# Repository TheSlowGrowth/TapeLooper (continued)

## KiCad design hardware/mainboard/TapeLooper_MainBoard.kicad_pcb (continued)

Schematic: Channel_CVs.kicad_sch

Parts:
C901, C902, C904, C905, C906, C907, C909, C910: 1n; C_0603_1608Metric_Pad1.08x0.95mm_HandSolder
C903, C908: 100n; C_0603_1608Metric_Pad1.08x0.95mm_HandSolder
J901, J902, J903, J904, J905, J906, J907, J908: PJ398SM; THONKICONN
R901, R903, R907, R909, R913, R915, R919, R921: 100k; R_0603_1608Metric_Pad0.98x0.95mm_HandSolder
R902, R908, R914, R920: 78k7; R_0603_1608Metric_Pad0.98x0.95mm_HandSolder
R904, R910, R916, R922: 68k; R_0603_1608Metric_Pad0.98x0.95mm_HandSolder
R905, R911, R917, R923: 481k; R_0603_1608Metric_Pad0.98x0.95mm_HandSolder
R906, R912, R918, R924: 200k; R_0603_1608Metric_Pad0.98x0.95mm_HandSolder
U901, U902: MCP6004; SO-14_3.9x8.65mm_P1.27mm

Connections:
+5VA: J902.2 (TN), J904.2 (TN), J906.2 (TN), J908.2 (TN); also elsewhere on the board
-10V: R905.2, R906.2, R911.2, R912.2, R917.2, R918.2, R923.2, R924.2; also elsewhere on the board
unnamed: J901.3 (T), R901.1
unnamed: J902.3 (T), R903.1
unnamed: J903.3 (T), R907.1
unnamed: J904.3 (T), R909.1
unnamed: J905.3 (T), R913.1
unnamed: J906.3 (T), R915.1
unnamed: J907.3 (T), R919.1
unnamed: J908.3 (T), R921.1
unnamed: C901.1, R901.2, R902.1, R905.1, U901.2 (-)
unnamed: C902.1, R903.2, R904.1, R906.1, U901.6 (-)
unnamed: C904.1, R907.2, R908.1, R911.1, U901.9 (-)
unnamed: C905.1, R909.2, R910.1, R912.1, U901.13 (-)
unnamed: C906.1, R913.2, R914.1, R917.1, U902.2 (-)
unnamed: C907.1, R915.2, R916.1, R918.1, U902.6 (-)
unnamed: C909.1, R919.2, R920.1, R923.1, U902.9 (-)
unnamed: C910.1, R921.2, R922.1, R924.1, U902.13 (-)
PITCH_A: C901.2, R902.2, U901.1; also elsewhere on the board
PITCH_B: C904.2, R908.2, U901.8; also elsewhere on the board
PITCH_C: C906.2, R914.2, U902.1; also elsewhere on the board
PITCH_D: C909.2, R920.2, U902.8; also elsewhere on the board
VOLUME_A: C902.2, R904.2, U901.7; also elsewhere on the board
VOLUME_B: C905.2, R910.2, U901.14; also elsewhere on the board
VOLUME_C: C907.2, R916.2, U902.7; also elsewhere on the board
VOLUME_D: C910.2, R922.2, U902.14; also elsewhere on the board

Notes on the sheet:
Pitch D
Pitch B
Volume D
-2 .. 2V
Volume A
Pitch C
0 .. 5V
Volume B
Pitch A
Volume C

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
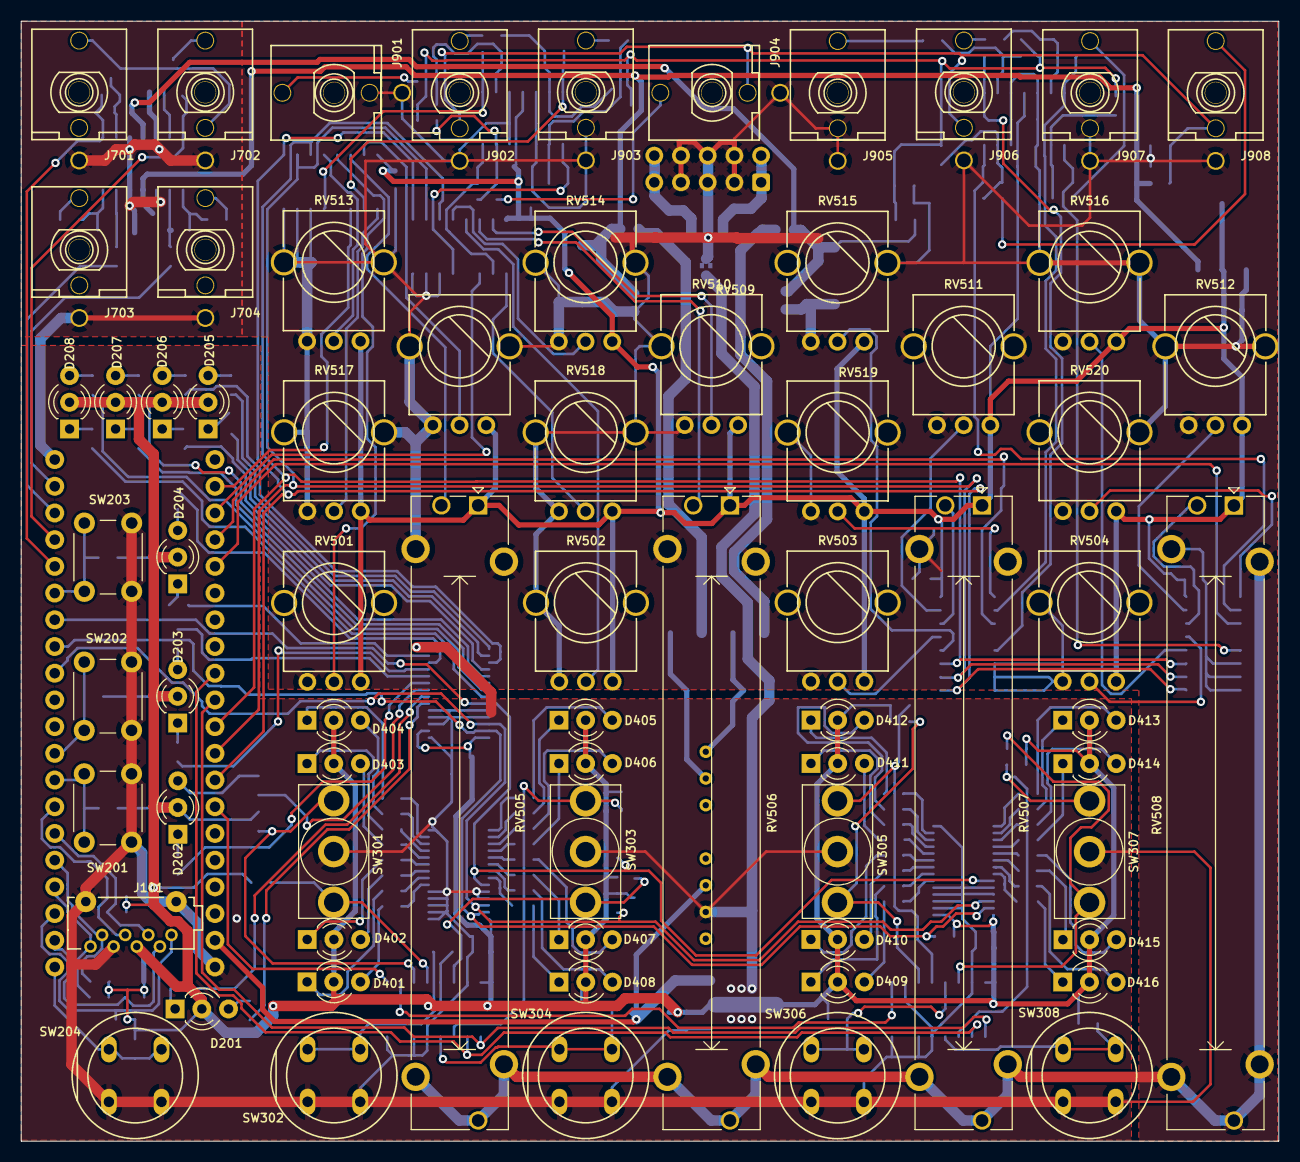
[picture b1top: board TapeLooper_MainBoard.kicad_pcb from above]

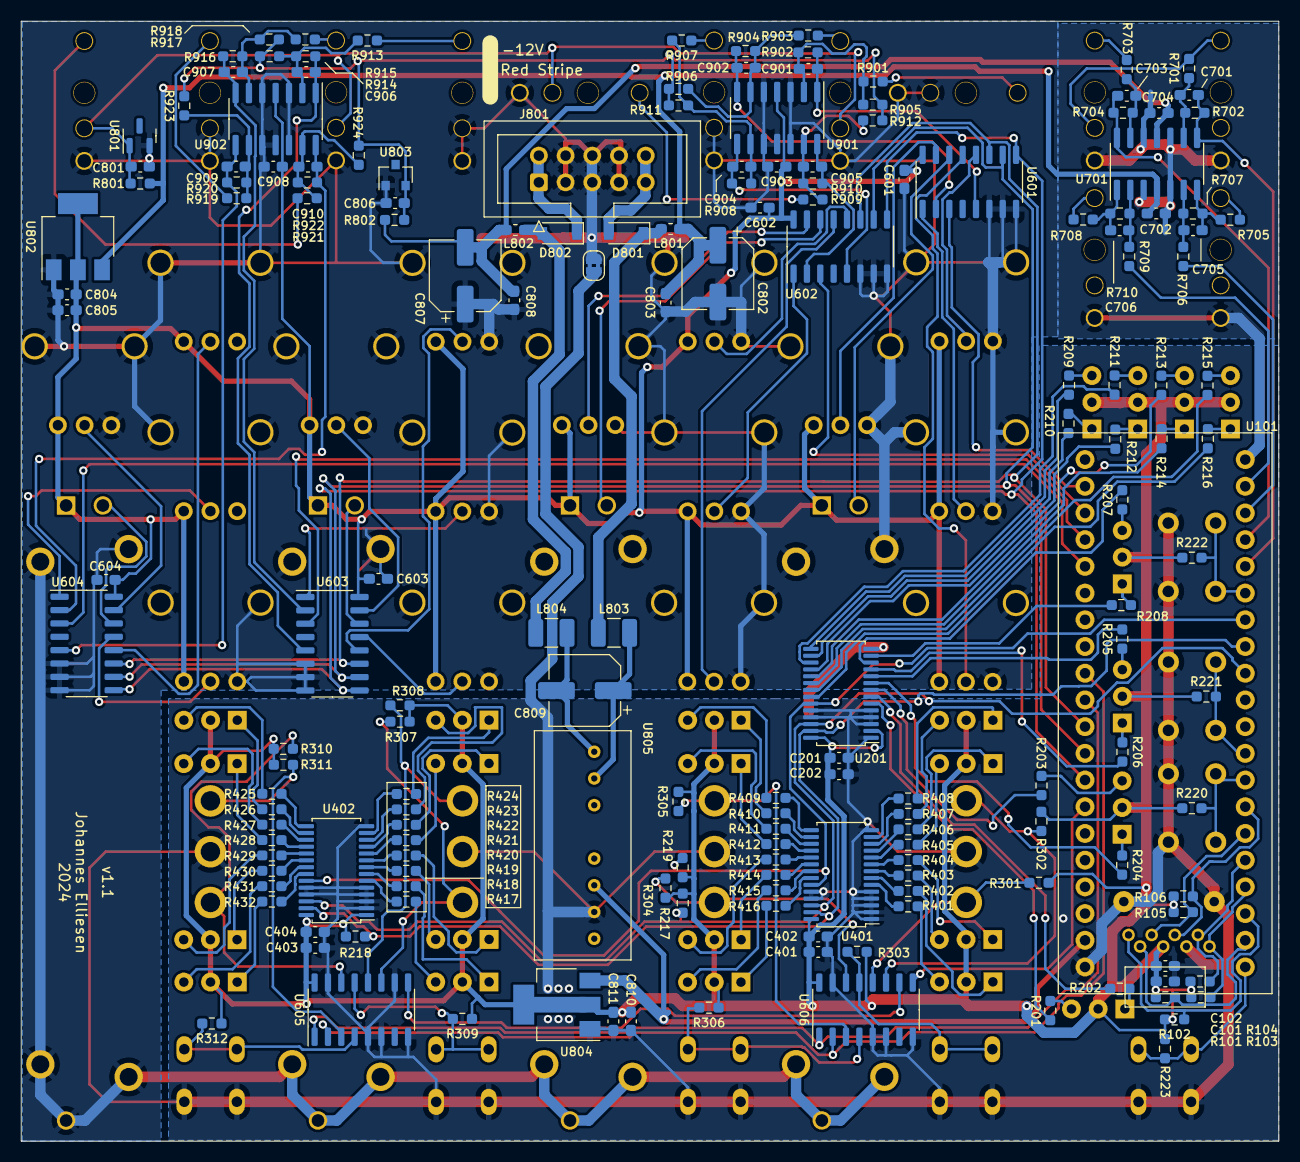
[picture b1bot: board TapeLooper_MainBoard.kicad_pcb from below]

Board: 2 copper layers, 119.6 x 106.5 mm, 243 parts (174 on the bottom side), 205 nets.

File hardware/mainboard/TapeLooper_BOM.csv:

"Reference","Value","Datasheet","Footprint","Qty","DNP"
"C101,C201,C401,C403","10u","","Capacitor_SMD:C_0603_1608Metric_Pad1.08x0.95mm_HandSolder","4",""
"C102,C202,C402,C404,C601,C602,C603,C604,C702,C704,C803,C804,C808,C810,C903,C908","100n","-- mixed values --","Capacitor_SMD:C_0603_1608Metric_Pad1.08x0.95mm_HandSolder","16",""
"C701,C703,C705,C706","560p","","Capacitor_SMD:C_0603_1608Metric_Pad1.08x0.95mm_HandSolder","4",""
"C801,C805,C806,C811","4u7","~","Capacitor_SMD:C_0603_1608Metric_Pad1.08x0.95mm_HandSolder","4",""
"C802,C807,C809","47u","","Capacitor_SMD:CP_Elec_6.3x5.8","3",""
"C901,C902,C904,C905,C906,C907,C909,C910","1n","~","Capacitor_SMD:C_0603_1608Metric_Pad1.08x0.95mm_HandSolder","8",""
"D201,D202,D203,D204,D205,D206,D207,D208,D401,D402,D403,D404,D405,D406,D407,D408,D409,D410,D411,D412,D413,D414,D415,D416","LED_RED_GREEN_CA","~","LED_THT:LED_D3.0mm-3","24",""
"D801,D802","1N5819","http://www.vishay.com/docs/88525/1n5817.pdf","Diode_SMD:D_SOD-123","2",""
"J101","Micro_SD_Card","http://katalog.we-online.de/em/datasheet/693072010801.pdf","ell_connectors:PJS008U-3000","1",""
"J701,J702,J703,J704,J901,J902,J903,J904,J905,J906,J907,J908","PJ398SM","","ell_connectors:THONKICONN","12",""
"J801","Conn_02x05_Odd_Even","~","Connector_IDC:IDC-Header_2x05_P2.54mm_Vertical","1",""
"JP801","SolderJumper_2_Bridged","~","Jumper:SolderJumper-2_P1.3mm_Bridged2Bar_RoundedPad1.0x1.5mm","1",""
"L801,L802","Bead","","Inductor_SMD:L_0603_1608Metric_Pad1.05x0.95mm_HandSolder","2",""
"L803,L804","4.7mH","~","Inductor_SMD:L_1210_3225Metric_Pad1.42x2.65mm_HandSolder","2",""
"R101,R102,R103,R104,R105,R106,R219","47k","~","Resistor_SMD:R_0603_1608Metric_Pad0.98x0.95mm_HandSolder","7",""
"R201,R202,R203,R204,R205,R206,R207,R208,R209,R210,R211,R212,R213,R214,R215,R216,R401,R402,R403,R404,R405,R406,R407,R408,R409,R410,R411,R412,R413,R414,R415,R416,R417,R418,R419,R420,R421,R422,R423,R424,R425,R426,R427,R428,R429,R430,R431,R432","330","~","Resistor_SMD:R_0603_1608Metric_Pad0.98x0.95mm_HandSolder","48",""
"R217,R218","4k7","~","Resistor_SMD:R_0603_1608Metric_Pad0.98x0.95mm_HandSolder","2",""
"R220,R221,R222,R223,R301,R302,R303,R304,R305,R306,R307,R308,R309,R310,R311,R312","10k","~","Resistor_SMD:R_0603_1608Metric_Pad0.98x0.95mm_HandSolder","16",""
"R701,R703,R707,R710,R901,R903,R907,R909,R913,R915,R919,R921","100k","-- mixed values --","Resistor_SMD:R_0603_1608Metric_Pad0.98x0.95mm_HandSolder","12",""
"R702,R704,R706,R709","8k2","","Resistor_SMD:R_0603_1608Metric_Pad0.98x0.95mm_HandSolder","4",""
"R705,R708","1k","","Resistor_SMD:R_0603_1608Metric_Pad0.98x0.95mm_HandSolder","2",""
"R801,R802","2k2","~","Resistor_SMD:R_0603_1608Metric_Pad0.98x0.95mm_HandSolder","2",""
"R902,R908,R914,R920","78k7","~","Resistor_SMD:R_0603_1608Metric_Pad0.98x0.95mm_HandSolder","4",""
"R904,R910,R916,R922","68k","~","Resistor_SMD:R_0603_1608Metric_Pad0.98x0.95mm_HandSolder","4",""
"R905,R911,R917,R923","481k","~","Resistor_SMD:R_0603_1608Metric_Pad0.98x0.95mm_HandSolder","4",""
"R906,R912,R918,R924","200k","~","Resistor_SMD:R_0603_1608Metric_Pad0.98x0.95mm_HandSolder","4",""
"RV501,RV502,RV503,RV504,RV509,RV510,RV511,RV512,RV513,RV514,RV515,RV516,RV517,RV518,RV519,RV520","POTENTIOMETER","","ell_passives:9mm_pot","16",""
"RV505,RV506,RV507,RV508","PTA4543-2010CPB103","~","Potentiometer_THT:Potentiometer_Bourns_PTA4543_Single_Slide","4",""
"SW201,SW202,SW203","TL1105SPF250Q","~","Button_Switch_THT:SW_PUSH_6mm","3",""
"SW204","D6R40F1LFS","~","ell_special:CK-D6R_Pushbutton","1",""
"SW301,SW303,SW305,SW307","C&K 7105SYCQE","~","ell_special:7105SYCQE-1P3T-SP3T-Switch","4",""
"SW302,SW304,SW306,SW308","D6R90F1LFS","~","ell_special:CK-D6R_Pushbutton","4",""
"U101","DAISY_SEED","","ell_special:Daisy_Seed","1",""
"U201,U401,U402","PCA9685PW","http://www.nxp.com/documents/data_sheet/PCA9685.pdf","Package_SO:TSSOP-28_4.4x9.7mm_P0.65mm","3",""
"U601,U602,U603,U604","4051","http://www.intersil.com/content/dam/Intersil/documents/cd40/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","Package_SO:SO-16_3.9x9.9mm_P1.27mm","4",""
"U605,U606","74HC165","https://assets.nexperia.com/documents/data-sheet/74HC_HCT165.pdf","Package_SO:SO-16_3.9x9.9mm_P1.27mm","2",""
"U701","TL074","-- mixed values --","Package_SO:SOIC-14_3.9x8.7mm_P1.27mm","1",""
"U801","LM4040DBZ-5","http://www.ti.com/lit/ds/symlink/lm4040-n.pdf","Package_TO_SOT_SMD:SOT-23","1",""
"U802,U804","AZ1117-3.3","https://www.diodes.com/assets/Datasheets/AZ1117.pdf","Package_TO_SOT_SMD:SOT-223-3_TabPin2","2",""
"U803","LM4040DBZ-10","http://www.ti.com/lit/ds/symlink/lm4040-n.pdf","Package_TO_SOT_SMD:SOT-23","1",""
"U805","EC4SAW-24S05N","","ell_special:EC4SAW_DC_DC_SIP8","1",""
"U901,U902","MCP6004","http://ww1.microchip.com/downloads/en/DeviceDoc/21733j.pdf","Package_SO:SO-14_3.9x8.65mm_P1.27mm","2",""

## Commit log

2021-08-09 add .gitignore
2021-08-09 add libDaisy submodule
2021-08-09 add googletest submodule
2021-08-09 add unit test skeleton
2021-08-09 add _clang-format
2021-08-09 add sprout library
2021-08-09 add firmware skeleton
2021-08-09 add github action workflows (formatting / firmware build / unit tests)
2021-08-09 add vscode config files
2021-09-18 add Recorder
2021-09-22 add gmock to the unit test setup
2021-09-22 add Player
2021-09-22 move libraries
2021-09-22 move _clang-format
2021-09-23 update libDaisy
2021-09-23 remove boost dependency from dsp/lib/sprout
    (probably breaking some of it's boost-related code, but we don't care)
2021-09-23 add second gtest executable for firmware sources
2021-09-23 extract dsp code into library
2021-09-23 build firmware with CMake
2021-09-23 update vscode configuration files
2021-09-23 add JUCE submodule (v6.1.2)
2021-09-23 add JUCE plugin skeleton
2021-09-28 fix crash when Player playback length < 1
2021-09-28 add TapeProcessor skeleton
2021-09-28 add samplerate template argument to Recorder
2021-09-28 add TapeLooper
2021-09-28 fix dsp library CMakeLists.txt
2021-09-28 disable fail-fast strategy for formatting CI jobs
2021-09-28 add sudo apt-get update step to ubuntu CI job
2021-09-28 add basic looper plugin
2021-10-09 add pre processor gain in addition to post processor gain
2021-10-09 add plateauMap()
2021-10-28 add License; update Readme
2021-10-28 fix plateau map tests
2021-10-28 add Tape DSP
2021-10-28 add badges to readme
2021-10-31 add multichannel support
2021-11-03 add util/Memory.h
2021-11-03 add save & recall to the plugin
2021-11-03 add launch config for the standalone plugin
2021-11-16 update vscode config
2021-11-20 fix broken firmware launch config
2021-11-20 generate debug symbols in release builds
2021-11-21 add missing MANUAL_INLINE
2021-11-21 remove high shelf emphasis EQ to save processing cycles
2021-11-21 switch to 44.1kHz (WIP - squash libDaisy Update!)
2021-11-21 remove pre gain
    (can be added to processor if required)
2021-11-21 increase Wow&Flutter amount
2021-11-21 add loopers to firmware for load testing
2021-11-27 add KiCad projects and frontpanel SVG
2021-11-27 ci: only build plugin, when plugin code was changed
2021-11-27 update licenses
2021-11-28 fix test launch config to work on apple silicon
2021-12-02 feat: extract TapeProcessor::Parameters into common class without template arguments
2021-12-03 feat: add arithmetic operations to AudioBufferPtr
2021-12-03 allow multiple types in LateInitializedObject
2022-01-25 feat: add LooperController
2022-01-25 chore: formatting
2022-01-25 refactor: move wow and flutter amount to Player.h
2022-01-25 hardware: update schematics & add BOM
2022-01-25 feat: implement most of the UI
2022-01-25 feat: DSP parameter fine tuning
2022-01-25 Style: formatting
2022-01-25 feat: use new multi chip MAX11300 driver
2024-07-24 hardware: delete obsolete KiCad 5 files
2024-07-24 chore: remove Fortran entries from .gitignore
2024-07-24 chore: add more KiCad files to .gitignore
2024-07-24 hardware: swap MAX11300 for ordinary multiplexers; PCB v1.1
2024-07-25 chore: cleanup tasks.json
2024-08-10 chore: update libDaisy to a feature branch
2024-08-10 feat: add muxed-adc based CV and knob driver
2024-08-10 feat: add shift register based button input driver
2024-08-10 feat: remove MAX11300 and GPIO initializations
2024-08-10 hardware: resave BOM in .csv format
2024-08-10 hardware: add missing SD card pullups
2024-08-10 hardware: fix resistor value
2024-08-10 hardware: fix reverse MCP6004 power pins
2024-08-10 feat: allow to abort a recording immediately
    this will be used when we want to restore a sample
    from storage while a recording is running
2024-08-10 hardware: change audio I/O gain slightly
2024-08-10 docs: correct voltage range in comment
2024-08-10 hardware: resave files with KiCad v8.0.4
2024-08-10 chore: fix .vscode configuration files
    new versions of the tools require a slightly different config
2024-08-10 feat: allow to prevent recording/playing in `TapeLooper`
    This will be used to lock the looper while we save/restore
    samples.
2024-08-10 style: remove whitespaces
2024-08-15 feat: Allow to set playback length without recording
    this will be needed when we restore samples and write
    them to the buffer directly
2024-08-15 hardware: ignore some irrelevant DRC errors
2024-08-15 feat: apply CV inputs to volume and pitch
2024-08-15 feat: Add more getters to `TapeLooper`
2024-08-16 chore: update libDaisy to v7.0.1
2024-08-16 hardware: resave files with KiCad v7.0.4
2024-08-16 refactor: expose KnobAndCvReader instead of raw CV values
2024-08-16 feat: add a calibration page
2024-08-16 feat: close settings page before entering calibration page
2024-08-16 feat: passthrough CV values
2024-08-16 feat: add CV calibration storage to UiHardware
2024-08-16 feat: implement calibration UI page
2024-09-04 tests: update existing UI tests
    They were not updated when the calibration feature was added.
    The "exit" tests are now split to make them less dependent on
    the behaviour of the other pages (we no longer have to go back
    to the page under test)
2024-09-04 chore: replace sprout library with gcem
    sprout is no longer maintained.
    gcem is slimmer and under active development.
2024-09-04 style: fix formatting
2024-09-04 refactor: move calibration data types to UiHardwareTypes
    So that we can compile the UI tests
2024-09-04 fix: avoid nullptr access when entering the settings page
2024-09-04 tests: add KnobsAndCvMock
2024-09-04 ci: use never cmake version
2024-09-04 ci: fix windows plugin builds
    by no longer using an old version of Visual Studio
    that is no longer present on windows-latest.
2024-09-04 chore: update launch config for plugin targets
2024-09-04 ci: fix mac plugin builds
2024-09-04 ci: fix overflow of flash memory in firmware build
    we were building a debug build; now we're building an optimized release build
2024-09-04 ci: update clang-format version
2024-09-04 fix: avoid duplicate symbol when compiling the plugin
2024-09-04 tests: add missing return
2024-09-04 ci: fix clang-format checks
    by no longer pinning jidicula/clang-format-action to an outdated version
2024-09-04 ci: update to actions/download-artifact@v3
2024-09-04 style: add some newlines in github actions yaml
2024-09-04 fix: make MANUAL_INLINE a bit more portable
2024-09-04 chore: add pre-commit hook for clang-format
2025-10-09 chore: update gcc-arm-none-eabi to version 10-2020-q4-major
2025-10-09 chore: update libDaisy to v8.0.0
2025-10-09 feat: LooperController can start save and recall
2025-10-09 feat: UiHardware provides array of all channel LEDs
2025-10-09 feat: implement UI pages for loading and saving
2025-10-09 feat: add WavFileFormat.cpp
2025-10-09 chore: run firmware tests in test folder to be able to access files there
2025-10-09 feat: Add empty `AudioSaveAndRecall`
2025-10-09 chore: Move some libDaisy stubs in tests to a dedicated header file
2025-10-09 feat: implement AudioSaveAndRecall
2025-10-09 feat: allow to set recording progress from tests
2025-10-09 fix: don't destroy never created object
    When calling `initializeToLayout` for the very first
    time, the `LateInitializedObject` wasn't initialized
    and we'd be calling the destructor of a dead object.
2025-10-09 chore: update Visual Studio version and github actions
2025-10-09 feat: main loop processes save or load operation
2025-10-09 feat: pass loop library into save and load ui pages
2025-10-09 chore: remove plugin
    The plugin isn't actively used anymore for development
    and will hopefully be replaced with a VCV rack version eventually.
    For now, let's remove the plugin to reduce the maintenance.
2025-10-09 refactor: extract file io ownership from `AudioSaveAndRecall`
2025-10-09 feat: extract loop library into its own class and namespace
2025-10-09 feat: Save and load pages show existing loops
2025-10-09 feat: implement fatfs based file IO
2025-10-09 chore: use a more up to date setup step in firmware CI build
2025-10-09 fixup! chore: update libDaisy to v8.0.0
2025-10-27 fixup! feat: implement fatfs based file IO
2026-01-12 dropme! Uncomment stuff to debug
2026-04-13 chore: update libDaisy to v8.1.0
2026-04-13 chore: add .cache to .gitignore
2026-05-22 fix: support hot plugging the SD card
    Reinitialization was previously not working because the
    SDMMC1 was stuck in a faulty state after it was detected
    that the SD card was removed.
    Resetting it fixes this issue.
    Now the SD card can be removed and plugged back in while
    the device is powered.
2026-05-22 chore: remove leftover JUCE submodule config
2026-05-22 chore: remove unused Makefile
2026-05-22 docs: update readme
